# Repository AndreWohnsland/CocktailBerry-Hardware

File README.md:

<br/>

CocktailBerry Hardware is the **official hardware repository** for the [CocktailBerry](https://github.com/AndreWohnsland/CocktailBerry) project.
It holds the machine designs (FreeCAD sources) and custom PCB(A)s (KiCad projects) you need to build your own CocktailBerry machine.

Build guides, parts lists, specifications, and downloadable fabrication files live in the
**[Hardware Documentation](https://hardware.cocktailberry.org/)**. For the software, setup, and
configuration, see the [main CocktailBerry project](https://github.com/AndreWohnsland/CocktailBerry)
and the [Software Documentation](https://software.cocktailberry.org/).

Like this project? Give the main repo a star on GitHub! ⭐

# Designs

Sources live in this repo; fabrication files (Gerbers/BOM/CPL for boards, STEP/STL for machines)
are generated from them by the build pipeline. Full specs, parts, and downloads are on the
[Hardware Documentation](https://hardware.cocktailberry.org/).

**PCBAs** ([`pcb/`](pcb)) — control boards that replace relay arrays, switching pump circuits via MOSFETs:

| Board                                                                                         | Description                          | Status   |
| --------------------------------------------------------------------------------------------- | ------------------------------------ | -------- |
| [CocktailBerryBoard GPIO](https://hardware.cocktailberry.org/pcbas/cocktailberry-board-gpio/) | GPIO-based, up to 10 circuits        | Released |
| [CocktailBerryBoard Slim](https://hardware.cocktailberry.org/pcbas/cocktailberry-board-slim/) | Compact GPIO-based, up to 8 circuits | Released |
| [CocktailBerryBoard I2C](https://hardware.cocktailberry.org/pcbas/cocktailberry-board-i2c/)   | I2C-based, up to 10 circuits         | Beta     |

**Machines** ([`cad/`](cad)) — 3D-printable machine builds:

| Machine                                                                  | Description                                            | Status   |
| ------------------------------------------------------------------------ | ------------------------------------------------------ | -------- |
| [CocktailBerry MK III](https://hardware.cocktailberry.org/machines/mk3/) | Compact footprint with integrated touchscreen support  | Released |
| [CocktailBerry 2-Go](https://hardware.cocktailberry.org/machines/2-go/)  | Portable Euro Box build with detachable legs           | Released |
| [CocktailBerry MK IV](https://hardware.cocktailberry.org/machines/mk4/)  | v2 reference build, optional scale + peristaltic pumps | Beta     |

# Contributing / How to Help

Contributions are very welcome - a new machine design, an improved model, or a PCB layout.
Open an issue or pull request.

**Please submit source files only:**

- PCBs: the KiCad project (`*.kicad_sch`, `*.kicad_pcb`, and any local symbols/footprints)
- Machines: the FreeCAD sources (`*.FCStd`)

Do **not** commit generated fabrication artifacts (Gerbers, drill, CPL, STL, STEP) - those are
built from the sources by the pipeline (see [`pcb/README.md`](pcb/README.md) and
[`cad/README.md`](cad/README.md)). See the main project's
[Contributing Guidelines](https://github.com/AndreWohnsland/CocktailBerry/blob/master/CONTRIBUTING.md)
for general rules.

# Related Projects

| Project                                                                        | Description                                |
| ------------------------------------------------------------------------------ | ------------------------------------------ |
| [CocktailBerry](https://github.com/AndreWohnsland/CocktailBerry)               | The main software project (Python + React) |
| [CocktailBerry Addons](https://github.com/AndreWohnsland/CocktailBerry-Addons) | Community addons and extensions            |
| [Software Documentation](https://software.cocktailberry.org/)                  | Software setup and configuration guides    |

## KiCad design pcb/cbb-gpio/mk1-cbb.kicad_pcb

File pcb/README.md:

# PCB

KiCad projects for the CocktailBerry boards (and room for other PCB-related
components later). JLCPCB fabrication files (Gerbers, drill, BOM, CPL) are
generated headlessly - on release by CI, or locally - with
[KiKit](https://github.com/yaqwsx/KiKit) via
[`scripts/build_fab.py`](../scripts/build_fab.py).

## Layout & conventions

```shell
pcb/<board>/
  <board>.kicad_pcb   # exactly one PCB per board folder
  <board>.kicad_sch   # root schematic (shares the project base name)
  *.kicad_sch         # hierarchical sub-sheets (e.g. a reused pump circuit)
  ...                 # symbols/footprints/etc. live alongside as usual
```

- Each board folder must contain **exactly one** `*.kicad_pcb` (one layout per
  project, no matter how many schematic sheets exist).
- **Hierarchical schematics are fine.** Only the **root** sheet (named after the
  project, like the `.kicad_pcb`) is passed to KiKit; it walks the hierarchy and
  pulls in all sub-sheets - so a pump circuit reused 10× flattens into the
  BOM/CPL automatically.
- Components to be assembled need their **LCSC part number** in the `MPN`
  schematic field (see `LCSC_FIELD` in `scripts/build_fab.py`). Parts without it
  appear in the BOM without an LCSC code and won't be placed.

## Running

KiKit + KiCad (`pcbnew`) are **not** uv dependencies; install them separately
(`apt-get install kicad` + `pip install kikit` on CI). Then:

```bash
uv run python scripts/build_fab.py            # all boards -> dist/<board>.zip
uv run python scripts/build_fab.py cbb-gpio    # a single board
```

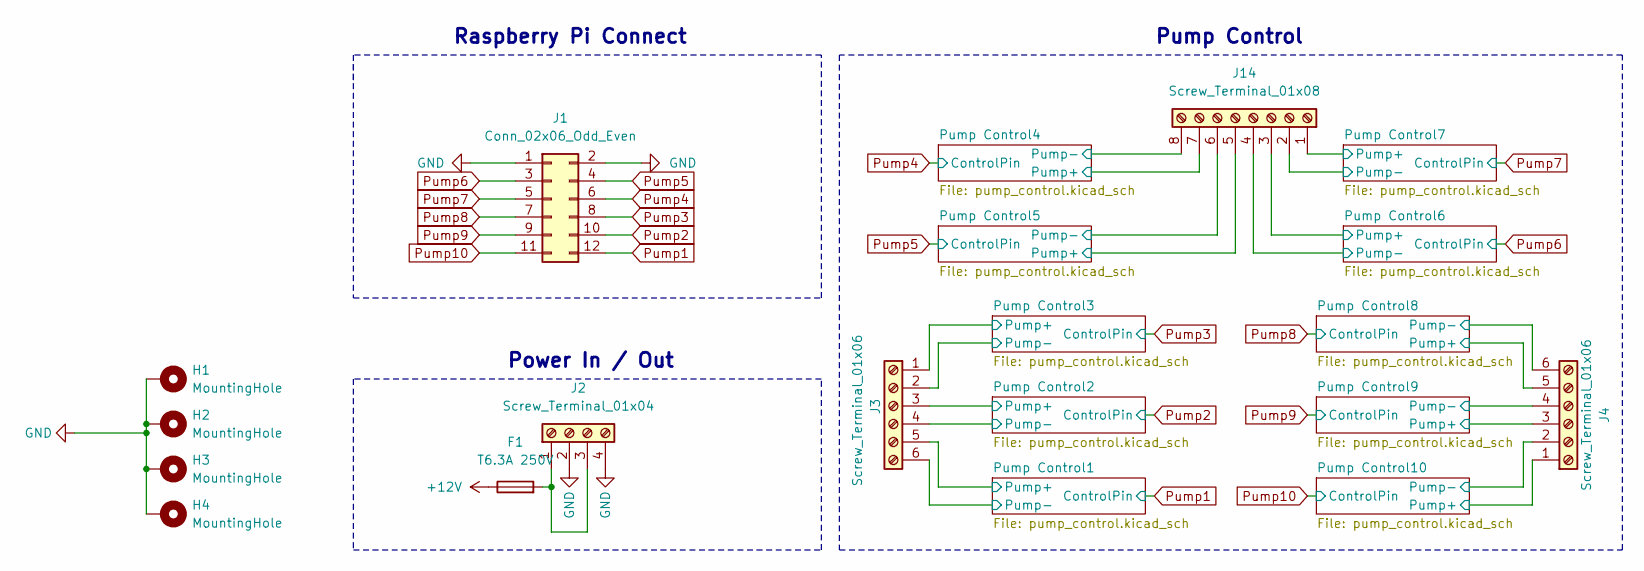
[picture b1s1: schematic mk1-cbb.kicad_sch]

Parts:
F1: T6.3A 250V; Fuse_Littelfuse_395Series; MPN C354907
H1, H2, H3, H4: MountingHole; MountingHole_2.7mm_M2.5_ISO7380_Pad
J1: Conn_02x06_Odd_Even; PinSocket_2x06_P2.54mm_Vertical; MPN C124388
J2: Screw_Terminal_01x04; TerminalBlock_Phoenix_MKDS-1,5-4_1x04_P5.00mm_Horizontal; MPN C430624
J3, J4: Screw_Terminal_01x06; TerminalBlock_Phoenix_MKDS-1,5-6_1x06_P5.00mm_Horizontal; MPN C20608945
J14: Screw_Terminal_01x08; TerminalBlock_Phoenix_MKDS-1,5-8_1x08_P5.00mm_Horizontal; MPN C430626

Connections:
+12V: F1.1, J3.1, J3.3, J3.5, J4.1, J4.3, J4.5, J14.1, J14.3, J14.5, J14.7; also elsewhere on the board
/Pump Control1/Pump-: J3.6; also elsewhere on the board
/Pump Control2/Pump-: J3.4; also elsewhere on the board
/Pump Control3/Pump-: J3.2; also elsewhere on the board
/Pump Control4/Pump-: J14.8; also elsewhere on the board
/Pump Control5/Pump-: J14.6; also elsewhere on the board
/Pump Control6/Pump-: J14.4; also elsewhere on the board
/Pump Control7/Pump-: J14.2; also elsewhere on the board
/Pump Control8/Pump-: J4.6; also elsewhere on the board
/Pump Control9/Pump-: J4.4; also elsewhere on the board
/Pump Control10/Pump-: J4.2; also elsewhere on the board
GND: H1.1, H2.1, H3.1, H4.1, J1.1, J1.2, J2.2, J2.4; also elsewhere on the board
unnamed: F1.2, J2.1, J2.3
Pump1: J1.12; also elsewhere on the board
Pump2: J1.10; also elsewhere on the board
Pump3: J1.8; also elsewhere on the board
Pump4: J1.6; also elsewhere on the board
Pump5: J1.4; also elsewhere on the board
Pump6: J1.3; also elsewhere on the board
Pump7: J1.5; also elsewhere on the board
Pump8: J1.7; also elsewhere on the board
Pump9: J1.9; also elsewhere on the board
Pump10: J1.11; also elsewhere on the board

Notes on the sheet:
Pump Control
Raspberry Pi Connect
Power In / Out

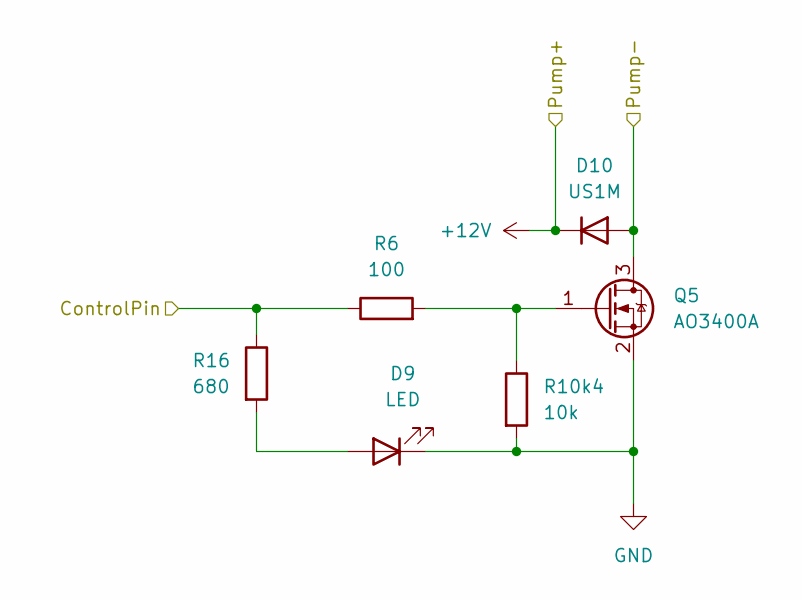
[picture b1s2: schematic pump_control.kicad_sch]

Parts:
D9: LED; LED_0603_1608Metric; MPN C2286
D10: US1M; D_SMA; MPN C412437
Q5: AO3400A; SOT-23; MPN C20917
R6: 100; R_0603_1608Metric; MPN C22775
R10k4: 10k; R_0603_1608Metric; MPN C25804
R16: 680; R_0603_1608Metric; MPN C23228

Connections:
+12V: D10.1 (K); also elsewhere on the board
/Pump Control10/Pump-: D10.2 (A), Q5.3 (D); also elsewhere on the board
GND: D9.1 (K), Q5.2 (S), R10k4.2; also elsewhere on the board
unnamed: D9.2 (A), R16.2
unnamed: Q5.1 (G), R6.2, R10k4.1
Pump10: R6.1, R16.1; also elsewhere on the board

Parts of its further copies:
D1, D3, D5, D7, D11, D13, D15, D17, D19: LED; LED_0603_1608Metric; MPN C2286
D2, D4, D6, D8, D12, D14, D16, D18, D20: US1M; D_SMA; MPN C412437
Q1, Q2, Q3, Q4, Q6, Q7, Q8, Q9, Q10: AO3400A; SOT-23; MPN C20917
R1, R3, R4, R5, R7, R8, R9, R10, R11: 100; R_0603_1608Metric; MPN C22775
R2, R10k1, R10k2, R10k3, R10k5, R10k6, R10k7, R10k8, R10k9: 10k; R_0603_1608Metric; MPN C25804
R12, R13, R14, R15, R17, R18, R19, R20, R21: 680; R_0603_1608Metric; MPN C23228

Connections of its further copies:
+12V: D2.1 (K), D4.1 (K), D6.1 (K), D8.1 (K), D12.1 (K), D14.1 (K), D16.1 (K), D18.1 (K), D20.1 (K); also elsewhere on the board
/Pump Control1/Pump-: D20.2 (A), Q10.3 (D); also elsewhere on the board
/Pump Control2/Pump-: D18.2 (A), Q9.3 (D); also elsewhere on the board
/Pump Control3/Pump-: D16.2 (A), Q8.3 (D); also elsewhere on the board
/Pump Control4/Pump-: D14.2 (A), Q7.3 (D); also elsewhere on the board
/Pump Control5/Pump-: D12.2 (A), Q6.3 (D); also elsewhere on the board
/Pump Control6/Pump-: D2.2 (A), Q1.3 (D); also elsewhere on the board
/Pump Control7/Pump-: D4.2 (A), Q2.3 (D); also elsewhere on the board
/Pump Control8/Pump-: D6.2 (A), Q3.3 (D); also elsewhere on the board
/Pump Control9/Pump-: D8.2 (A), Q4.3 (D); also elsewhere on the board
GND: D1.1 (K), D3.1 (K), D5.1 (K), D7.1 (K), D11.1 (K), D13.1 (K), D15.1 (K), D17.1 (K), D19.1 (K), Q1.2 (S), Q2.2 (S), Q3.2 (S), Q4.2 (S), Q6.2 (S), Q7.2 (S), Q8.2 (S), Q9.2 (S), Q10.2 (S), R2.2, R10k1.2, R10k2.2, R10k3.2, R10k5.2, R10k6.2, R10k7.2, R10k8.2, R10k9.2; also elsewhere on the board
unnamed: D1.2 (A), R12.2
unnamed: D3.2 (A), R13.2
unnamed: D5.2 (A), R14.2
unnamed: D7.2 (A), R15.2
unnamed: D11.2 (A), R17.2
unnamed: D13.2 (A), R18.2
unnamed: D15.2 (A), R19.2
unnamed: D17.2 (A), R20.2
unnamed: D19.2 (A), R21.2
unnamed: Q1.1 (G), R1.2, R2.1
unnamed: Q2.1 (G), R3.2, R10k1.1
unnamed: Q3.1 (G), R4.2, R10k2.1
unnamed: Q4.1 (G), R5.2, R10k3.1
unnamed: Q6.1 (G), R7.2, R10k5.1
unnamed: Q7.1 (G), R8.2, R10k6.1
unnamed: Q8.1 (G), R9.2, R10k7.1
unnamed: Q9.1 (G), R10.2, R10k8.1
unnamed: Q10.1 (G), R10k9.1, R11.2
Pump1: R11.1, R21.1; also elsewhere on the board
Pump2: R10.1, R20.1; also elsewhere on the board
Pump3: R9.1, R19.1; also elsewhere on the board
Pump4: R8.1, R18.1; also elsewhere on the board
Pump5: R7.1, R17.1; also elsewhere on the board
Pump6: R1.1, R12.1; also elsewhere on the board
Pump7: R3.1, R13.1; also elsewhere on the board
Pump8: R4.1, R14.1; also elsewhere on the board
Pump9: R5.1, R15.1; also elsewhere on the board

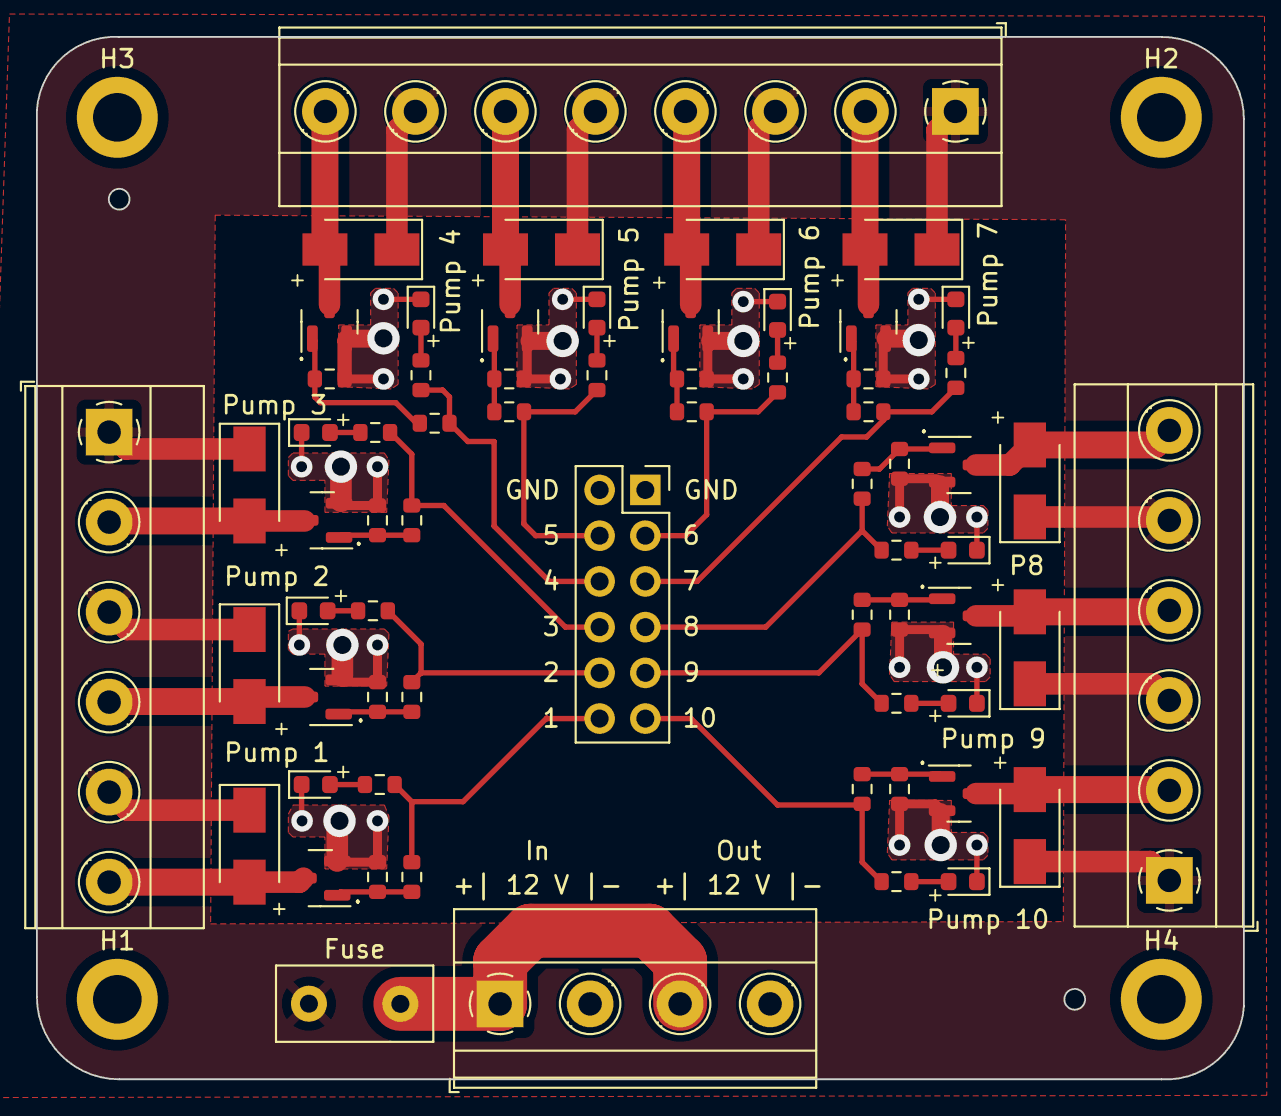
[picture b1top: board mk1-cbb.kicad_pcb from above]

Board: 2 copper layers, 67.1 x 57.9 mm, 70 parts (0 on the bottom side), 43 nets.

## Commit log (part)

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2026-06-06 add licence
2026-06-07 add base readme
2026-06-09 add base doc files
2026-06-09 fix naming
2026-06-10 start populating mk3 and cbb docs
2026-06-11 add base release pipeline
2026-06-16 first bodies test
2026-06-17 adjust freecad build steps
2026-06-17 optimize cicd outputs
2026-06-17 fix part naming
2026-06-17 add cad parameters
2026-06-17 add cocktailberry board gpio
2026-06-17 exclude parameters from build
2026-06-17 ignore backups
2026-06-17 add build optimization
2026-06-17 add correction file
2026-06-18 split manual build artifacts
2026-06-21 extend base skeletons for machines
2026-06-21 base docs and files for mk3
2026-06-23 add mk3 gpio recommendation
2026-06-25 Finalize mk3
2026-06-25 update cbb gpio
2026-06-25 add screws to mk3
2026-06-25 adjust shared docs section
2026-06-25 adjust pcb git
2026-06-26 add 2-go parts
2026-06-26 add build instructions for 2go
2026-06-26 restructure docs folder naming
2026-06-26 streamlined docs hyphens
2026-06-27 add docs for available pcbas
2026-06-27 add slim CBB
2026-06-27 combine 2go bodies
2026-06-28 adjust mk4 needed parts
2026-06-28 exclude shared folders for fab toolkit
2026-06-29 add first assembly image to mk4
